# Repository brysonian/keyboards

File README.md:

`Some custom keyboards`

1. From within the directory for the corresponding layout run `ergogen .` to generate the output.
2. To convert jscad to stl use:
    `npx @jscad/cli@1 {INPUT} -of stla -o {OUTPUT}.stl`
3. Use `dxf-to-svg` to, well, convert ergogen's DXF files to SVG

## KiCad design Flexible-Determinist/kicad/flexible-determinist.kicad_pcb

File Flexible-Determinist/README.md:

# Flexible-Determinist

This is the first keyboard i made, almost 100% from the excellent tutorial at https://flatfootfox.com/ergogen-part1-units-points/

## TODO
- Flip the feather so the USB is up
- Fix a few missing connections
- Less PCB padding

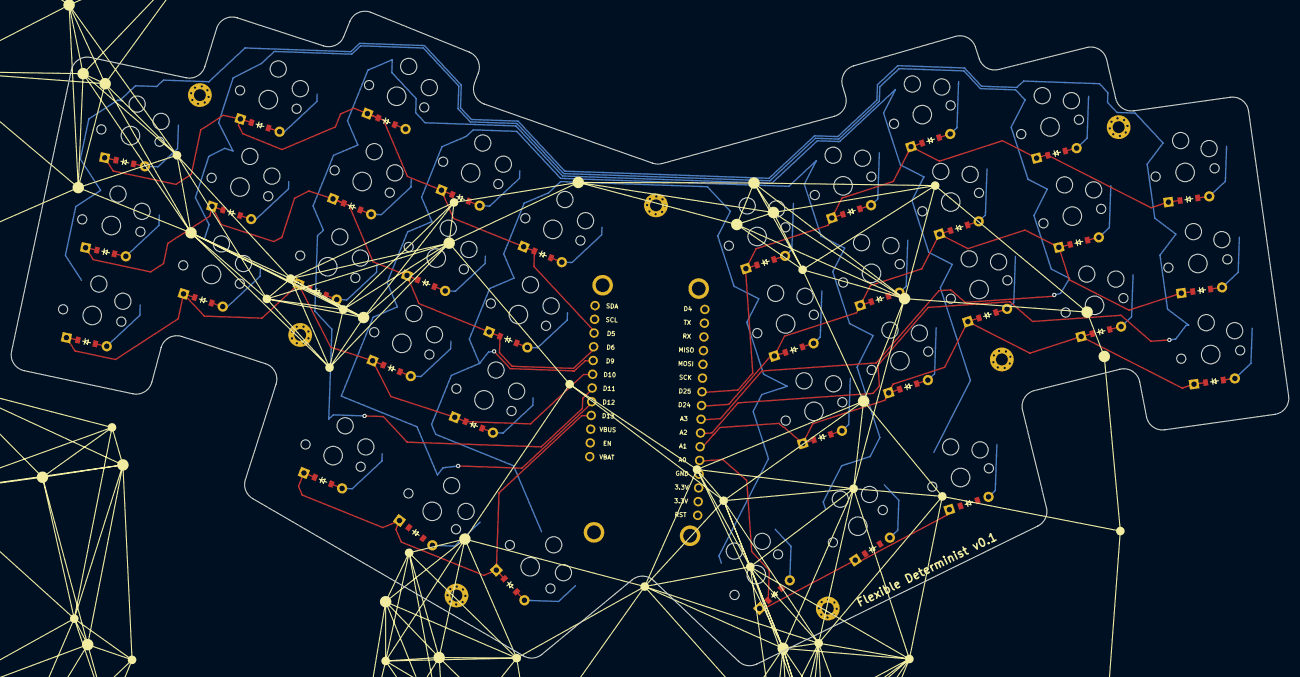
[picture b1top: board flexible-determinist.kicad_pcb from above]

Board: 2 copper layers, 236.2 x 121.0 mm, 80 parts (0 on the bottom side), 50 nets.

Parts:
D1, D2, D3, D4, D5, D6, D7, D8, D9, D10, D11, D12, D13, D14, D15, D16, D17, D18, D19, D20, D21, D22, D23, D24, D25, D26, D27, D28, D29, D30, D31, D32, D33, D34, D35, D36: ComboDiode
S1, S2, S3, S4, S5, S6, S7, S8, S9, S10, S11, S12, S13, S14, S15, S16, S17, S18, S19, S20, S21, S22, S23, S24, S25, S26, S27, S28, S29, S30, S31, S32, S33, S34, S35, S36: PG1350
_1: Feather_RP2040
_2, _3, _4, _5, _6, _7, _8: MountingHole_2.2mm_M2_Pad_Via

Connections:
A0: D34.1, D35.1, D36.1, _1.17
A1: D19.1, D22.1, D25.1, D28.1, D31.1, _1.18
A2: S1.1, S2.1, S3.1, S19.1, S20.1, S21.1, _1.19
A3: S4.1, S5.1, S6.1, S22.1, S23.1, S24.1, _1.20
D5: D3.1, D6.1, D9.1, D12.1, D15.1, _1.10
D6: D2.1, D5.1, D8.1, D11.1, D14.1, _1.9
D9: S13.1, S14.1, S15.1, S18.1, S31.1, S32.1, S33.1, S36.1, _1.8
D10: D1.1, D4.1, D7.1, D10.1, D13.1, _1.7
D11: S7.1, S8.1, S9.1, S16.1, S25.1, S26.1, S27.1, S34.1, _1.6
D12: S10.1, S11.1, S12.1, S17.1, S28.1, S29.1, S30.1, S35.1, _1.5
D13: D16.1, D17.1, D18.1, _1.4
D24: D20.1, D23.1, D26.1, D29.1, D32.1, _1.21
D25: D21.1, D24.1, D27.1, D30.1, D33.1, _1.22
V33: _1.14, _1.15
index_bottom: D10.2, S10.2
index_middle: D11.2, S11.2
index_top: D12.2, S12.2
inner_bottom: D13.2, S13.2
inner_middle: D14.2, S14.2
inner_top: D15.2, S15.2
middle_bottom: D7.2, S7.2
middle_middle: D8.2, S8.2
middle_top: D9.2, S9.2
mirror_index_bottom: D28.2, S28.2
mirror_index_middle: D29.2, S29.2
mirror_index_top: D30.2, S30.2
mirror_inner_bottom: D31.2, S31.2
mirror_inner_middle: D32.2, S32.2
mirror_inner_top: D33.2, S33.2
mirror_middle_bottom: D25.2, S25.2
mirror_middle_middle: D26.2, S26.2
mirror_middle_top: D27.2, S27.2
mirror_mod_cluster: D35.2, S35.2
mirror_outer_cluster: D34.2, S34.2
mirror_pinkie_bottom: D19.2, S19.2
mirror_pinkie_middle: D20.2, S20.2
mirror_pinkie_top: D21.2, S21.2
mirror_ring_bottom: D22.2, S22.2
mirror_ring_middle: D23.2, S23.2
mirror_ring_top: D24.2, S24.2
mirror_space_cluster: D36.2, S36.2
mod_cluster: D17.2, S17.2
outer_cluster: D16.2, S16.2
pinkie_bottom: D1.2, S1.2
pinkie_middle: D2.2, S2.2
pinkie_top: D3.2, S3.2
ring_bottom: D4.2, S4.2
ring_middle: D5.2, S5.2
ring_top: D6.2, S6.2
space_cluster: D18.2, S18.2

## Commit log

2025-05-31 ignore
2025-05-31 add readme and board
2025-05-31 add a package.json so we can have a handy build script
2025-06-01 update footprints
2025-06-07 add mounting holes
2025-06-21 reorganize src
2025-06-27 add firmware ignore backups and lcks
2025-06-29 update firmware
2025-07-30 move pcb to main level
2025-08-04 updated firmware
2025-08-04 add ignore so vscode shuts up
2025-08-04 formating
2025-09-11 firmware updates
2026-02-14 adding last firmware vers for FD
2026-02-14 updated FD firmware
2026-02-22 add taz firmware update FD firmware
2026-02-22 remove laser form
2026-02-22 add ignore
2026-02-22 update ignore
2026-02-22 remove tmp
2026-02-22 hakim
2026-02-22 quote update
2026-02-22 md fix
2026-02-22 point
2026-02-22 add link to firmware
